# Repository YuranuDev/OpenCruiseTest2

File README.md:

# OpenCruise — Qt + aasdk 車載システム 簡易プロトタイプ

x86_64 PC 向けの車載システム試作。Qt Quick(QML) + C++ + CMake。Android Auto の接続・映像は同梱の `aasdk` を利用する。
**完成品ではなく、各機能を最低限つないだ動作確認用の仮システム**。

## 構成

```
OpenCruise/
├── CMakeLists.txt            トップ。aasdk をサブプロジェクトとして取り込み、app/ をビルド
├── aasdk/                    既存の aasdk（※ USB/USBWrapper.cpp のみ 1 か所修正。後述）
├── patches/                  aasdk に当てた修正の diff
├── scripts/                  開発用スクリプト(make_test_stream.sh=テスト映像(H.264)の生成 / bootsplash/=起動画面)
├── docs/                     設計メモ・調査データ・スクリーンショット
│   ├── *.md                  実装ガイド・Android Auto 接続フローの仕様
│   ├── reference/            aasdk_phone_data.csv など調査データ
│   └── screenshots/          画面の確認用スクリーンショット
└── app/
    ├── CMakeLists.txt        アプリ本体のビルド設定(ソース・QML・リソースの登録はここ)
    ├── src/                  C++(#include は src/ からの相対パス。例: "audio/AudioSettings.h")
    │   ├── main.cpp          起動・モデル生成・QML 公開・開発用オプション
    │   ├── core/             アプリ基盤: AppInfo / AppSettings / BootManager / Log / UiText
    │   ├── audio/            音: AudioSettings / SystemSound / AlsaAudio / AlsaSoundEffect
    │   ├── display/          画面: BrightnessController / DisplaySettings / DrmDisplay
    │   ├── ui/               UI 支援: ThemeSettings / WidgetStore / ClockModel / AlbumArtProvider
    │   ├── vehicle/          車両: VehicleDataManager / ReverseCamera
    │   ├── system/           SystemStats(CPU・メモリ・温度など)
    │   ├── notification/     NotificationManager / NotificationHistoryModel
    │   ├── androidauto/      Qt 側: AndroidAutoController / H264Decoder / VideoSurfaceItem / TestVideoFeeder / PhoneStatus
    │   └── aabackend/        Qt 非依存の aasdk 接続層（UI と分離。無効時はスタブ）
    │       ├── AasdkBackend.*    libusb・ioスレッド・USBHub、待機→接続→切断→待機のループ
    │       ├── AasdkSession.*    1接続ぶん。制御チャネル(バージョン/SSL/認証/サービス探索/Ping/切断)
    │       ├── AasdkVideoHandler.* 映像チャネル(Open/Setup/Start/データ受信/ACK/フォーカス)
    │       └── AasdkConfig.h     車載機として申告する値（解像度 dpi 等、暫定値を1か所に集約）
    ├── qml/                  QML(すべて 1 つのモジュール OpenCruise。他フォルダの型を使うファイルは `import OpenCruise` が必要)
    │   ├── Main.qml          ルート(ここだけ qml/ 直下)
    │   ├── theme/            Theme(シングルトン) / ThemeBackground
    │   ├── components/       共通部品: Panel / ActionButton / MaterialIcon / NumberText / StatCard / MarqueeText など
    │   ├── screens/          画面: HomeScreen / LauncherScreen / SettingsScreen / SplashScreen / ReverseCamera*
    │   ├── settings/         設定の部品(Settings* / WSStepper / WSTextField)
    │   │   └── pages/        設定の各ページ(SettingsPage*)
    │   ├── osd/              OSD(音量・明るさ)と通知(NotificationPopup / Bell / HistoryPanel)・AlarmClearButton
    │   ├── services/         画面を持たないシングルトン: VehicleHistory / WarningAlarm
    │   └── widgets/          ウィジェット(下の「ウィジェット」参照)
    └── resources/            実行ファイルに入れる/隣へコピーする素材
        ├── images/           ロゴなど(qrc に埋め込む)
        ├── fonts/            アイコンフォント(qrc に埋め込む)と日本語フォント(ビルド時に実行ファイルの隣の fonts/ へコピー)
        └── sounds/           効果音(ビルド時に実行ファイルの隣の sounds/ へコピー)
```

接続層 (`aabackend`) は Qt を一切含まず、UI は `AasdkBackend` の公開ヘッダだけを見る。
そのため aasdk が無い/接続できない環境でもアプリ全体が起動する（状態は「利用不可」「待機中」と表示）。

## ビルド

Ubuntu 24.04 で確認。必要パッケージ:

```bash
sudo apt install build-essential cmake ninja-build pkg-config \
  qt6-base-dev qt6-declarative-dev qml6-module-qtquick qml6-module-qtquick-controls \
  qml6-module-qtquick-layouts qml6-module-qtquick-window qml6-module-qtquick-templates \
  qml6-module-qtqml qml6-module-qtqml-workerscript \
  qt6-multimedia-dev qml6-module-qtmultimedia \
  libavcodec-dev libavutil-dev libswscale-dev \
  libboost-system-dev libboost-log-dev libprotobuf-dev protobuf-compiler libusb-1.0-0-dev libssl-dev \
  libasound2-dev
# 日本語表示用フォント（例）
sudo apt install fonts-noto-cjk

cmake -G Ninja -S . -B build -DCMAKE_BUILD_TYPE=Release
ninja -C build            # aasdk(約300ファイル)を含むため初回は数分〜十数分
./build/app/opencruise
```

- aasdk なしで UI だけビルド: `-DOPENCRUISE_ENABLE_AASDK=OFF`（Boost/libusb/protobuf 不要）
- aasdk は同梱のものを `SKIP_BUILD_PROTOBUF=ON` / `SKIP_BUILD_ABSL=ON`（システムの protobuf 3.21 を使用）でビルドする。
  Abseil が必要な新しい protobuf を使う場合はこの設定の見直しが必要。
- 実機接続には USB 権限が必要。aasdk の `DOCUMENTATION.md` にある udev ルール
  (`SUBSYSTEM=="usb", ATTR{idVendor}=="18d1", MODE="0666", GROUP="plugdev"`) を設定する。
  権限が無い場合、aasdk の `USBHub` は **エラーを出さず黙って無視する**ため、「待機中」のまま進まない。

### 開発用オプション

| オプション | 内容 |
|---|---|
| `--test-video <file>` | H.264 ファイルを映像として表示（スマホ無しでデコード/表示を確認）。`scripts/make_test_stream.sh` で生成 |
| `--screenshot <png> [--screenshot-delay <ms>]` | 画面を保存して終了 |
| `--open-settings` | 設定画面を開いた状態で起動 |
| `--fullscreen` | 全画面 |

ヘッドレス確認例: `QT_QPA_PLATFORM=offscreen QT_QUICK_BACKEND=software ./build/app/opencruise --screenshot out.png`

## 音量・明るさ

設定の「サウンド」「表示」から変更できるほか、キーボード(将来はステアリングスイッチ等)のショートカットで操作できる。

| ショートカット | 内容 |
|---|---|
| `Ctrl+Shift+V` / `Ctrl+Shift+B` | マスター音量を 5 % 下げる / 上げる(V = Volume。押しっぱなしで連続)。マスター音量と、マップ音声・音楽音声・システムの各音量バーをまとめて表示し、約 2.5 秒で自動で閉じる。表示中のバーはすべてタッチ/ドラッグで直接変更でき、押している間は閉じない |
| `Ctrl+Shift+K` / `Ctrl+Shift+L` | 画面の明るさを 10 % 下げる / 上げる(L = Light)。現在値のバーを表示し、約 2 秒で自動で閉じる |

すべて `Ctrl+Shift+文字` で統一している(将来の物理ボタンも、同じキーイベントを送れば同じ動作になる)。
音量・明るさは、隣り合う 2 つのキーで「左のキー = 下げる、右のキー = 上げる」にそろえている。
既存のキー(`Esc` / `F10` / `Menu` / `Meta`・`Super` / `Ctrl+Shift+D`)とは重ならない組み合わせにしてある。
メディアキーや `Ctrl+Alt+矢印` は、OS 側の音量・画面回転と二重に動くため使っていない。

- **マスター音量**(`audio/AudioSettings`): 3 つの音声系統すべてに掛かる共通の倍率(0〜100 %)。各系統の個別音量の設定値は変えずに保持する。
  再生器へ渡す値は `AudioSettings::gain(group)` の 1 か所で「個別 × マスター」に合成しており、`AudioPlayer` / `SystemSound` はこれだけを使う
  (マスターを別に掛けないこと。二重になる)。マイク(入力)は対象外。保存キーは `audio/masterVolume`。
- **画面の明るさ**(`display/BrightnessController`): 10〜100 %(0 にして画面が見えなくなるのを防ぐ)。保存キーは `display/brightness`。
  - Linux で `/sys/class/backlight/*/brightness` に書き込める場合は、バックライトを直接制御する。
  - 書き込めない場合(Windows、権限なし、外部ディスプレイなど)や書き込みに失敗した場合は、画面全体に黒い幕を重ねて暗くする方式に自動で切り替わる。
    どちらか一方だけを使うので、二重に暗くはならない。
  - バックライトを制御するには、そのファイルへ書き込める権限が必要(例: udev ルールでグループ書き込みを許可)。
  - バックライトは、保存された設定がある場合だけ起動時に値を反映する。終了時に元の値へは戻さない。

### 音の出し方(ALSA)

libasound(`libasound2-dev`)があるビルドでは、音を ALSA の機器へ直接出す・録る(PulseAudio / PipeWire を通さない。`audio/AlsaAudio`)。
設定の出力先・マイクの一覧は ALSA の機器(サウンドカードの PCM ごと。「システム既定」は ALSA の `default`)。
機器は音を出している間このアプリが使う(占有する。音が止まって 3 秒たつと手放す)が、アプリ内の音(マップ・音楽・システム・効果音)は
アプリの中で混ぜてから出すので、同じ機器を選んでも同時に鳴り、音量も別々。別々の機器にも分けられる。
効果音は `AlsaSoundEffect` で鳴らす(WAV は自前で読み、MP3 は QAudioDecoder で読む)。カードの抜き差しは `/proc/asound` を見て一覧を読み直す。
libasound が無いビルド(Windows など)は、これまでどおり Qt の音声入出力を使う。ログは `[AUDIO]`。
## テーマと背景

設定「表示 > テーマ」でアプリ全体の見た目を選べる(`ui/ThemeSettings`、QML では `themeSettings`。色と形は `qml/theme/Theme.qml`)。

| テーマ | 内容 |
|---|---|
| シンプル | これまでの見た目(平らな面・大きめの角丸・青のアクセント) |
| クラシック | 2000 年代ごろの車の内装に合う見た目。ガンメタ(夜)/シルバー(昼)の面に、ゆるいグラデーションと内側の細いハイライト、小さめの角丸。アクセント色(照明色)はアンバー・赤・青・緑・アイボリー・シアン |

背景(設定「表示 > 背景」): テーマに合わせる(シンプルは無地、クラシックはカーボン)/ 無地 / 模様(カーボン・ヘアライン・パンチング・ストライプ)/ 画像。
画像は `~/.local/share/OpenCruise/backgrounds` に PNG / JPEG を置くと選べる(並べる・画面を埋める・引き伸ばす)。濃さも変えられる。
面(カード・ボタン・ダイアログ)は `qml/components/Panel.qml` を使うと、テーマに合わせて描き分けられる。

### 飾りの画像(キャラなど)

初期画面のページごとに、好きな画像を好きな場所へ置ける(ウィジェットの後ろ・パネルの上・前、ステータスバーやナビバーの上も)。

1. `~/.local/share/OpenCruise/decorations` に画像(PNG / JPEG / WebP / GIF。キャラだけを置くなら透過 PNG)を入れる
2. 初期画面の「編集」→ 上のバーの「画像」→「画像を追加」で選ぶ(今のページの中央に置かれる)
3. ドラッグで移動(画面の中央・端に近づくと吸い付いて線が出る)。大きさは右下のつまみか、2 本指でつまむ(縦横比はそのまま)
4. 選ぶと下に操作パネルが出る: 濃さ・左右反転・重ね方・いちばん上へ・複製・削除(2 回押し)。上のバーの「元に戻す」で 1 つずつ戻せる

重ね方:

| 重ね方 | 出る場所 |
|---|---|
| 奥 | ウィジェット・バーの後ろ(ウィジェットの隙間から見える) |
| パネル | 各ウィジェットのパネル(カード)の上、メーターや文字の下。画面の同じ所にある画像が、パネルの形に切り抜かれて見える |
| 手前 | ウィジェットの前(タッチは下のウィジェットへ通す) |

「パネル」の角丸の切り抜きは、Qt 6.5 以降の MultiEffect、無ければ Qt5Compat の OpacityMask(`qml6-module-qt5compat-graphicaleffects`)を使う。
どちらも無いとき・ソフトウェア描画のときは四角く切り抜く(パネルの角の丸みの外へ少しはみ出る)。

置いた場所は `widgetStore.layoutJson` のページごとの `decor` に、画面に対する割合で保存する(画面の大きさが変わっても同じ所に出る)。
画像が見つからないものは、編集中だけ赤い枠で出る(消せる)。Android Auto 画面には出ない。
実装: `qml/widgets/DecorationStore.qml`(今のページの一覧・元に戻す)/ `DecorationLayer.qml`(奥・手前の表示)/
`DecorationPanelLayer.qml`(パネルの層。WidgetBase の中)/ `DecorationEditor.qml`・`DecorationPanel.qml`(置き直す操作)/
`DecorationPicker.qml`(追加パネル)。

## バックカメラ

バック信号が入ると、どの画面でもカメラの映像(全面)に切り替わり、切れると設定の秒数のあとで元の画面に戻る(`vehicle/ReverseCamera`、
QML では `reverseCamera`。画面は `qml/screens/ReverseCameraView.qml`、設定は「設定 > カメラ」)。

- バック信号: 今はダミーだけ。**Ctrl+Shift+R** か、設定の「ダミーのバック信号」で入/切する。
  将来の外部マイコン(バックランプの線を読む)からの入力は `ReverseCamera::setExternalReverse()` で受け、入力元を「外部」にする(通信は未実装)
- カメラ: Qt Multimedia の映像入力(Linux では V4L2)。UVC で認識されるキャプチャーボード・USB カメラを設定から選ぶ
  (機器の id で保存。「自動」は最初に見つかったもの。選んだ機器が抜けているときは、ほかのカメラに替えず「見つかりません」と出す)。
  形式は 1280x720 以下でいちばん大きく、フレームレートの高いものを選ぶ
- 映し方: 左右反転・ガイド線(距離の目安)・全体を表示 / 画面を埋める・すぐに映す(常にカメラを動かしておく)
- 映像の上には、左上にギアの表示(R・バック)、上の中央に警告マークつきの「周囲の安全を直接確認してください」を出す。
  バック中は閉じるボタンを出さない(信号が切れたら戻る)。設定の「映像を確認」で、バック信号なしで映像を確かめられる(右上の「確認を終わる」で戻る)
- 実行には `qml6-module-qtmultimedia` が要る。ログは `[CAMERA]`

## ウィジェット

初期画面の中央領域は、12 × 6 マスのウィジェット配置エリアになっている(時計・あいさつも、その中のウィジェット)。

| 操作 | 内容 |
|---|---|
| 長押し(約 0.3 秒)→ドラッグ | 持ち上げて移動。移動中だけ配置エリア(グリッド)と移動先の枠が滑らかに現れ、離すと最寄りの空きマスへスナップ。空きマスが無ければ元の位置へ戻る |
| ダブルタップ | 設定画面を持つウィジェットは設定ダイアログ(固有の設定 + サイズ + 削除)を開く |
| ナビバーの「編集」 | 編集モードに入る・出る(下記) |

編集モード(ナビバーの「編集」。Android Auto 画面ではメニューの「編集」):

| 操作 | 内容 |
|---|---|
| 上の編集バー | 「編集中」・ページの切り替え・選んだ数と操作(まとめて設定・削除・選択を解除)・このページを選択・全ページを選択・追加・完了。削除は 2 回押し |
| ページをまたいだ選択 | ページを移っても選択は残る(選んだ数は全ページの分。「2 個選択中(2 ページ)」)。「全ページを選択」→「まとめて設定」で、全ページのウィジェットの見た目をまとめて変えられる |
| ウィジェットをタップ | 選択 / 解除(グリッドが出て、各ウィジェットに名前と大きさ「3 x 2」が出る。中身は操作できない) |
| ウィジェットをドラッグ | すぐ移動(長押しは要らない)。選んだものの 1 つを動かすと、選択中のものが並びを保ってまとめて動く |
| 左上の丸いボタン(歯車) | そのウィジェットの設定 |
| 右上の丸いボタン(×) | 削除(1 回目で赤い「削除」に広がり、0.4〜3 秒の間にもう一度押すと消す) |
| まとめて設定 | 選んだウィジェットに同じ値を入れる。同じ種類だけならその種類の設定すべて、混ざっていれば共通の項目(枠・上部タイトル)だけ。範囲・単位・警告値・注意値・目盛り間隔・タイトル文字・サイズはそれぞれのまま |
| Android Auto の映像(Android Auto 画面) | ドラッグで置く角を、内側の角のつまみで大きさ(マス数)を変える。離したときに決まる |

追加パネル(編集バーの「追加」)は、ジャンル別タブ。「初期配置に戻す」も、ここ(2 回押しで実行)。

配置と設定は `QSettings`(`widgets/layout`、version つき JSON)へ保存する。

### ファイル構成(`app/qml/widgets/`)

| 場所 | 役割 | ファイル |
|---|---|---|
| `framework/` | 登録(新しいウィジェットを足すときに触る唯一の場所) | `WidgetRegistry.qml`(ジャンル・種類・既定サイズ/設定・初期配置) |
| `framework/` | 共通基盤 | `WidgetBase`(ウィジェットの土台) / `WidgetHost`(ドラッグ・スナップ・タップ振り分け・表示アニメーション) / `WidgetArea`(グリッド・衝突・保存) / `WidgetPages` / `PageBar` / `PageMenu` / `WidgetEditBar` |
| `framework/` | 設定・追加 UI | `WidgetSettingsBase` / `WidgetSettingsDialog` / `WidgetSettingsGroup` / `WidgetPicker`(入力部品の `WSStepper` / `WSTextField` は `settings/`) |
| `decoration/` | 装飾 | `Decoration*`(Store / Layer / Panel / PanelLayer / Editor / Picker / Effects) |
| `clock/` `greeting/` | 時計・あいさつ | `ClockWidget` / `GreetingWidget`(+ 各 `*Settings`) |
| `gauge/` `graph/` | 車載連携 | `GaugeWidget` / `GaugeSettings`(メーター共通。ターボ圧計・タコメーター・スピードメーター・水温計・燃料計。計測値の定義は `WidgetRegistry.gaugeSpecs`。アナログ+デジタル、単位切替、警告値・警告メッセージ。**モックデータ**) / `GraphWidget` / `GraphSettings` |
| `phonestatus/` | Android Auto 連携 | `PhoneStatusWidget`(スマホ状態。バッテリー残量は実データ、電波はモック) |
| `phonenotice/` `phonecall/` | 通知・通話連携 | `PhoneNoticeWidget`(スマホ通知。表示方法・カテゴリ別メッセージを設定可能。**モックの通知**) / `PhoneCallWidget` |
| `nowplaying/` `navigation/` | 再生中・ナビ | `NowPlayingWidget` / `NavigationWidget`(+ 各 `*Settings`) |

新しいウィジェットの追加手順: ① `widgets/<名前>/` フォルダを作り、`WidgetBase` を継承した qml を置く ② 設定が要るなら `WidgetSettingsBase` を継承した qml を作る
③ `WidgetRegistry.qml` に Component と `types` の 1 項目を足す ④ `app/CMakeLists.txt` の `QML_FILES` に足す(他フォルダの型を使うなら `import OpenCruise` を書く)。
設定が不要なウィジェットは `settings: null` にする(ダブルタップは何もしない)。独自のダブルタップ動作が欲しい場合は
`doubleTapAction: "custom"` にして `doubleTapped()` を受ける。

### Android Auto から取れる情報(`docs/reference/aasdk_phone_data.csv` の確認結果)

- 実データ: スマホのバッテリー(残量・残り時間・危険フラグ。`BatteryStatusNotification`。サービス宣言なしで届く)。`AasdkSession` →
  `AndroidAutoController` → `PhoneStatus::setBattery()`。バッテリー残量の単位(%)は実機での確認が必要。
- 未宣言のため届かない(現状モック): 電波強度(PhoneStatus サービス)、通知(GenericNotification サービス: id / text / icon のみ)、
  ナビ・再生中の曲。宣言を足したら `PhoneStatus::setSignal()` / `ingestNotice()` を呼ぶだけでウィジェットは実データに切り替わる。
- そもそも取れない: 通知の送信元アプリ名・本文、連絡先・通話履歴・メッセージ本文(プロトコルに無い)。通知のカテゴリは文面から推定する。

## 実装状況

### 実装済み

| 機能 | 状態 | 検証 |
|---|---|---|
| Qt Quick メイン画面（暗色、時計、接続状態、AA表示領域、CANパネル、設定ボタン） | 実装 | ビルド・起動・画面保存で確認 |
| 現在時刻表示 | 実装(時計ウィジェットへ移行) | 画面で確認(旧実装) |
| ウィジェットシステム(配置エリア・ドラッグ・スナップ・設定ダイアログ・追加パネル、時計/あいさつ/ターボ圧計/スマホ状態/スマホ通知) | コード実装 | **ビルド・実行とも未検証** |
| CAN 情報の仮表示（速度/回転数/水温/燃料、「ダミーデータ」と明示） | 実装 | 画面で確認 |
| 設定画面への遷移（StackView） | 実装 | 設定画面の描画を確認。ボタンのタップ操作は未確認 |
| 接続状態表示（利用不可/待機中/接続中/接続済み/映像受信中、切断理由の保持） | 実装 | 「利用不可」「待機中」「映像受信中(テスト)」を画面で確認 |
| 未接続・失敗時でもアプリ全体が起動 | 実装 | aasdk 無効/有効(USB機器なし)の両方で確認 |
| H.264 デコード → QImage → QML 表示 | 実装 | テスト映像(800x480)で表示を確認（aasdk 非経由） |
| aasdk 接続層（USBHub→AOAP→Messenger→制御/映像チャネル→切断→待機復帰） | **コード実装・ビルド成功** | **実機未検証** |
| 終了処理（スレッド停止・libusb 解放） | 実装 | 待機中の終了(約0.2秒)を確認。セッション中の終了は未検証 |
| マスター音量・音量ショートカット・音量表示 | コード実装 | **ビルド・実行とも未検証** |
| 画面の明るさ(設定・ショートカット・表示。バックライト/暗幕の自動切替) | コード実装 | **ビルド・実行とも未検証** |

### 検証できたこと / できていないこと

確認できた: aasdk を含むフルビルド成功(自作コードの警告 0)、起動と待機状態への遷移、10秒間の待機稼働、
サービス探索応答が protobuf として必須フィールドを満たすこと(`IsInitialized()`)、デコード/表示経路。

**未検証（実機が必要。「動作済み」とは扱わない）**: スマートフォンの検出、AOAP 切替、SSL ハンドシェイク、サービス探索の受理、
映像チャネルのセットアップ、実際の H.264 受信と表示、ACK の運用、切断時の復帰、再接続。

### aasdk が提供するもの / 追加実装したもの

| aasdk が提供 | 本プロジェクトで追加実装 |
|---|---|
| USB ホットプラグ検出・AOAP 切替 (`USBHub`) | libusb の初期化と **イベントループ専用スレッド**、io スレッド、待機⇄接続のループ |
| USB 転送・フレーム化・SSL 暗号化 (`USBTransport`/`Messenger`/`Cryptor`) | セッションの組み立てと終了処理 |
| チャネルの送受信と protobuf デコード（制御/映像） | **各メッセージへの応答ロジック**（ハンドシェイク手順、サービス探索応答の内容、Open/Setup/Start 応答、ACK、フォーカス応答、Ping） |
| 映像データの受信（H.264 の生バイト列まで） | **H.264 デコード**（FFmpeg）と画面表示 |

同梱の `aasdk/tools/simple` は AOAP ハンドシェイクのスタブで、Messenger/映像は含まない。完全なセッションの手順は
ヘッダ・実装・`.proto` から読み取った（根拠は各 `.cpp` 冒頭のコメントに記載）。

### 未実装

- 実 CAN 通信（ダミーのみ）
- タッチ入力・ステアリング操作の転送（InputSource）、センサー(走行状態等)、音声（再生/マイク）、Bluetooth、無線接続(Wi-Fi/TCP)
- 車載機側からの Ping 送信・タイムアウト検出
- 解像度/dpi の最適化（800x480・140dpi の暫定値。`AasdkConfig.h`）、GPU 描画（現状は `QQuickPaintedItem` のソフトウェア描画）
- 設定の保存、画面の多言語化（UI 文字列は日本語直書き）

## aasdk で見つけた問題と対処

1. **`USBWrapper::hotplugRegisterCallback` のダングリングポインタ（修正済み）**
   スタック上のハンドルのアドレスを `shared_ptr` に渡していたため、`USBHub::cancel()` でホットプラグコールバックが解除されず、
   破棄済みの `USBHub` に通知が飛ぶ恐れがあった。切断後に `USBHub` を作り直す設計に必須のため、ヒープ確保に修正
   （`patches/aasdk-usb-hotplug-handle.patch`。aasdk を更新する場合は再適用が必要）。
2. `Messenger::stop()` は受信キューを空にするだけで保留中の Promise を失敗させない → `transport->stop()` によるキャンセル経由で終了を伝播させている。
3. `Cryptor::deinit()` 後に `encrypt()` が呼ばれると `SSL*` が null でクラッシュし得る → 最後の参照者が消えた時に `deinit()` する（カスタムデリータ）。
4. バージョン応答の status は `uint16` を `MessageStatus` に単純キャストしており不一致値が `-1` にならない → 「`STATUS_SUCCESS` 以外は失敗」で判定。
5. `USBHub` は USB 機器の open 失敗を黙殺し、非 AOAP 機器の検出ごとに 1 秒 sleep する → io スレッドを 2 本にして影響を緩和。権限エラーは UI から判別できない。
6. `ControlServiceChannel::sendVoiceSessionFocusResponse` は実装が空（Promise が解決されない）→ 使っていない。

## 実機検証の際の見どころ（リスク）

- サービス探索で**映像サービスのみ**申告している。センサー/入力サービスが無いとスマートフォンが接続を維持しない可能性がある（未確認）。
  切断された場合は `AasdkVideoHandler::fillFeatures` と同様に `SensorSource`/`InputSource` の追加を検討する。
- `driver_position` は右ハンドル、音声フォーカス要求には「喪失」、ナビフォーカスには PROJECTED を返す暫定実装。
- ログは `[aa] [session] ...` `[aa] [video] ...` として標準エラーに出る。どこまで進んだかの切り分けに使える。
- `--test-video` で映像が出ても aasdk の受信が動いた証拠にはならない（状態表示に「aasdk 経由ではありません」と出る）。

## 使用素材・ライセンス

### 効果音: OtoLogic

アプリの効果音(`app/resources/sounds/`)には、[OtoLogic](https://otologic.jp) が配布している素材音源を使用しています。

- 素材: OtoLogic (https://otologic.jp)
- ライセンス: [CC BY 4.0](https://creativecommons.org/licenses/by/4.0/deed.ja)
- 利用規約: https://otologic.jp/free/license.html

素材を再配布するとき(このリポジトリを配布する場合も含む)は、このクレジット表記を引き継いでください。

### 音声: AivisSpeech

起動時のあいさつなどの音声(`app/resources/sounds/start/` の読み上げ音声)は、[AivisSpeech](https://aivis-project.com) で作成しました。

- AivisSpeech 本体: 生成した音声にクレジット表記の義務はありません(任意のクレジットとして記載しています)
- 音声合成モデル: 使ったモデルごとのライセンスに従います。AivisHub などで公開されている ACML / ACML-NC / CC0 のモデルは
  クレジット表記の義務がありません。ACML-NC のモデルは非商用に限られるため、商用で配布する場合はモデルのライセンスを確認してください
- 使用した音声合成モデル: (モデル名とライセンスを記入)

### クレジットの表示場所

アプリの画面内にも、同じクレジットを表示しています(設定 > 情報 > 使用素材・ライセンス)。

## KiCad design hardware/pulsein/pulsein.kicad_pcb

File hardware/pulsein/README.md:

# パルス入力アダプター PULSE-IN v1.0

関連：claude/power-board-design.md（v1.8）、claude/firmware-config-spec.md（v1.6）、claude/spice-verification.md（tb7）
KiCadデータ：OpenCruiseTest2/hardware/pulsein（生成スクリプト：gen/pulsein_sch.py、place_pulsein.py、route_pulsein.py、silk_pulsein.py、flow_pulsein.sh）

## 目的
車速パルス・タコ信号・外付けセンサーのパルスを、XIAO ESP32S3で読める3.3Vの信号に変換する。メイン基板は変更せず、J8／J9（JST-XH 4P）に小基板をつなぐ方式にした。

- 1枚で1チャンネル。J8につなげばD2、J9につなげばD3に入る（2チャンネルまで）
- 3チャンネル目以降は、J5（D6・D7・D10と5V・12V・GND）からケーブルで分岐すればつなげる。パルスの読み取りにアナログ入力は不要なので、D6・D7も使える

## 仕様
| 項目 | 値 |
|---|---|
| 入力 | 0〜16Vの方形波（プッシュプル）、またはオープンコレクタ（JP1でプルアップ） |
| しきい値 | 立ち上がり約1.8V／立ち下がり約1.0V（JP2を閉じると約5.8V／3.2V） |
| 周波数 | 〜約10kHz（入力のRCフィルタ τ=22µs） |
| 耐圧 | 22kの直列抵抗と4.7Vツェナーで保護。40Vのスパイクでも74LVC1G17の入力は4.7V前後（SPICE tb7） |
| 出力 | 3.3Vロジック（74LVC1G17のプッシュプル、100Ω直列） |
| 表示 | パルスに合わせてLEDが点滅する（配線確認用） |
| センサー用電源 | J2から5V（メインのF5 0.25A）と12V（VSW、メインのF4 1.1A）を出す |
| 外形 | 34×28mm、2層、M3穴1個 |

## 回路
- J2（入力、XH 4P）：1 SIG_IN／2 GND／3 +5V／4 +12V
- JP1（3端子ソルダージャンパー）：1-2で5Vプルアップ、2-3で12Vプルアップ（R1 4.7k）。初期は開放
- R2 22k → SIG_A。C1 1nF、DZ1 BZT52C4V7でGNDへ
- R3 10k＋JP2：閉じるとしきい値が上がる（ノイズの多い12V信号向け）。**5V／3.3Vの信号では閉じない**（入力が届かず、出力が出なくなる。SPICEで確認済み）
- U1 74LVC1G17（3.3V動作、シュミット）→ R4 100Ω → J1-4
- U2 XC6206P332（5V→3.3V）、C2・C3 1µF、C4 100nF
- R5 1k＋D1 LED：パルスの表示
- J1（メイン基板へ、XH 4P）：1 +12V（VSW_EXT）／2 +5V（5V_EXT）／3 GND／4 OUT。**メイン基板のJ8/J9と同じ並びなので、ストレートのXH 4Pケーブルでつなぐ**

## 信号ごとのジャンパー設定（目安）
| 信号 | JP1 | JP2 | 備考 |
|---|---|---|---|
| 車速パルス（12V方形波） | 開放 | 開放（ノイズが多ければ閉じる） | 実車で波形を確認する |
| 車速パルス（オープンコレクタ） | 1-2（5V）または2-3（12V） | 2-3のときだけ閉じてよい | テスターで、つないでいないときの電圧を見ると判別できる |
| タコ信号（12V方形波） | 開放 | 閉じる | |
| 外付けセンサー（5V／3.3V出力） | 開放 | 開放 | センサー電源はJ2の5Vから取れる |
| 外付けセンサー（オープンコレクタ） | 1-2（5V） | 開放 | |

## 製造（JLCPCB）
- jlc/pulsein_gerber_JLC.zip、jlc/pulsein_BOM_JLC.csv（12品目14点）、jlc/pulsein_CPL_JLC.csv
- J1・J2（JST XH B4B-XH-A）は、メイン基板と同じくAliExpressで買って手はんだする（BOMとCPLから除外）
- U1のLCSC番号はメイン基板のU5と同じ（C151394）。DZ1 BZT52C4V7（C173408）だけが拡張部品
- 検査：ERC 0件、DRC 違反0・未接続0、シルクとパッドの距離0.22mm以上（JLCの基準0.18mm以上）

## 実車での確認事項
- Keiの車速パルスとタコ信号の取り出し位置、波形（電圧・プッシュプルかオープンコレクタか）
- 車速パルスの1kmあたりのパルス数（日本車は2548パルス/kmが多い。GPSで合わせる）
- タコ信号の1回転あたりのパルス数（3気筒は1.5パルス/回転が多いが、車種で異なる）

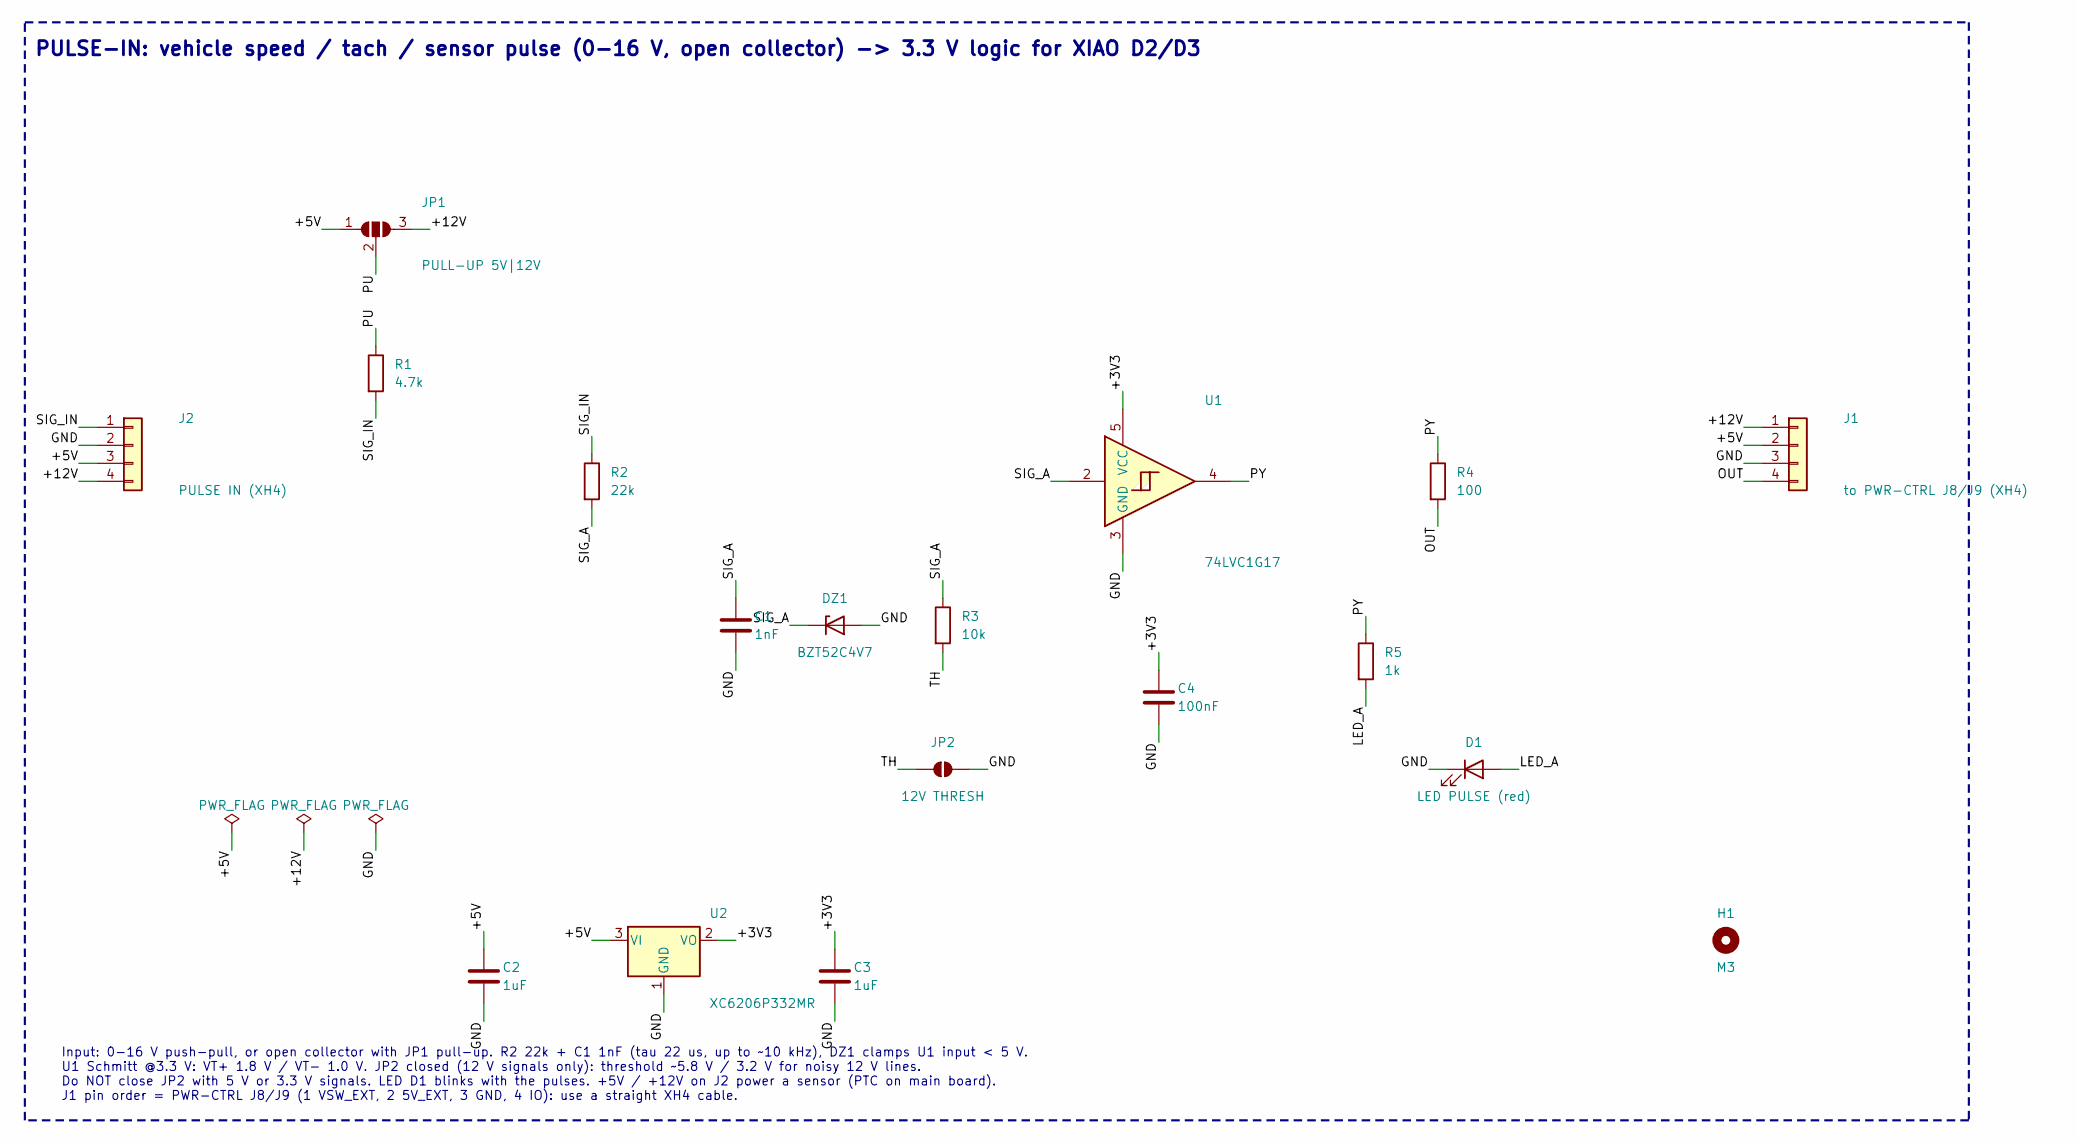
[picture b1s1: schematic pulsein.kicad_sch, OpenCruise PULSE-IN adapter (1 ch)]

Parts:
C1: 1nF; C_0603_1608Metric; LCSC C1588
C2, C3: 1uF; C_0603_1608Metric; LCSC C15849
C4: 100nF; C_0603_1608Metric; LCSC C14663
D1: LED PULSE (red); LED_0603_1608Metric; LCSC C2286
DZ1: BZT52C4V7; D_SOD-123; LCSC C173408
H1: M3; MountingHole_3.2mm_M3
J1: to PWR-CTRL J8/J9 (XH4); JST_XH_B4B-XH-A_1x04_P2.50mm_Vertical; LCSC C144395
J2: PULSE IN (XH4); JST_XH_B4B-XH-A_1x04_P2.50mm_Vertical; LCSC C144395
JP1: PULL-UP 5V|12V; SolderJumper-3_P1.3mm_Open_RoundedPad1.0x1.5mm
JP2: 12V THRESH; SolderJumper-2_P1.3mm_Open_RoundedPad1.0x1.5mm
R1: 4.7k; R_0603_1608Metric; LCSC C23162
R2: 22k; R_0603_1608Metric; LCSC C31850
R3: 10k; R_0603_1608Metric; LCSC C25804
R4: 100; R_0603_1608Metric; LCSC C22775
R5: 1k; R_0603_1608Metric; LCSC C21190
U1: 74LVC1G17; SOT-23-5; LCSC C151394
U2: XC6206P332MR; SOT-23; LCSC C5446

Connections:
+3V3: C3.1, C4.1, U1.5 (VCC), U2.2 (VO)
+5V: C2.1, J1.2, J2.3, JP1.1 (A), U2.3 (VI)
+12V: J1.1, J2.4, JP1.3 (B)
GND: C1.2, C2.2, C3.2, C4.2, D1.1 (K), DZ1.2 (A), J1.3, J2.2, JP2.2 (B), U1.3 (GND), U2.1 (GND)
LED_A: D1.2 (A), R5.2
OUT: J1.4, R4.2
PU: JP1.2 (C), R1.1
PY: R4.1, R5.1, U1.4
SIG_A: C1.1, DZ1.1 (K), R2.2, R3.1, U1.2
SIG_IN: J2.1, R1.2, R2.1
TH: JP2.1 (A), R3.2

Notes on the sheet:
PULSE-IN: vehicle speed / tach / sensor pulse (0-16 V, open collector) -> 3.3 V logic for XIAO D2/D3
Input: 0-16 V push-pull, or open collector with JP1 pull-up. R2 22k + C1 1nF (tau 22 us, up to ~10 kHz), DZ1 clamps U1 input < 5 V. U1 Schmitt @3.3 V: VT+ 1.8 V / VT- 1.0 V. JP2 closed (12 V signals only): threshold ~5.8 V / 3.2 V for noisy 12 V lines. Do NOT close JP2 with 5 V or 3.3 V signals. LE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

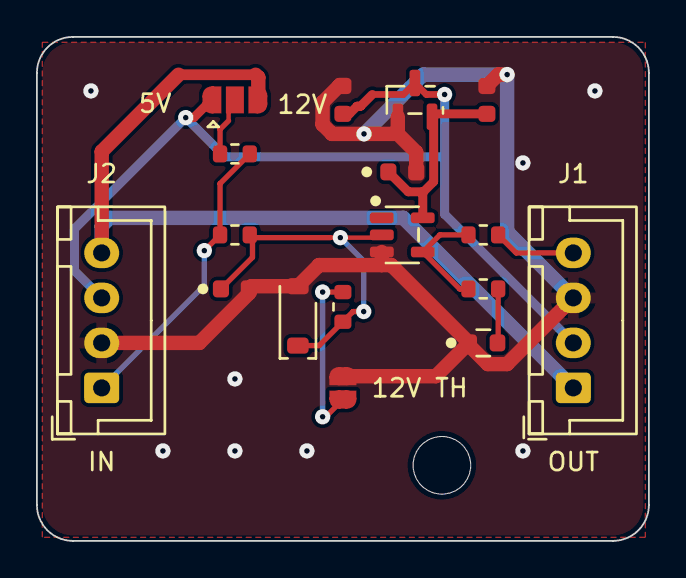
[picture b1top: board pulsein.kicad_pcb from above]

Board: 2 copper layers, 34.0 x 28.0 mm, 18 parts (0 on the bottom side), 11 nets.

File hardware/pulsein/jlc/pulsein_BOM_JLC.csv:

Comment,Designator,Footprint,LCSC Part #
1nF,"C1",C_0603_1608Metric,C1588
1uF,"C2,C3",C_0603_1608Metric,C15849
100nF,"C4",C_0603_1608Metric,C14663
LED PULSE (red),"D1",LED_0603_1608Metric,C2286
BZT52C4V7,"DZ1",D_SOD-123,C173408
4.7k,"R1",R_0603_1608Metric,C23162
22k,"R2",R_0603_1608Metric,C31850
10k,"R3",R_0603_1608Metric,C25804
100,"R4",R_0603_1608Metric,C22775
1k,"R5",R_0603_1608Metric,C21190
74LVC1G17,"U1",SOT-23-5,C151394
XC6206P332MR,"U2",SOT-23,C5446

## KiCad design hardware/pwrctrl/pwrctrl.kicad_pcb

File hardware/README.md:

# OpenCruise hardware (KiCad 9)

- pwrctrl/  : main power-control / vehicle-interface board (schematic + placement-proposal PCB, NOT routed yet)
- usbblock/ : USB-A inline VBUS back-feed blocker adapter (schematic)
- lib/      : project symbol/footprint library (OpenCruise) and 3D models
- gen/      : Python generators used to build the schematics/placement (kicad-cli + pcbnew 9.0)

Status v1.7 (2026-11-09): schematics complete, ERC 0 errors / 0 warnings. PCB layout pending review of placement_proposal.png.
Design notes: Claude project docs claude/power-board-design.md, firmware-config-spec.md, usb-adapter-design.md

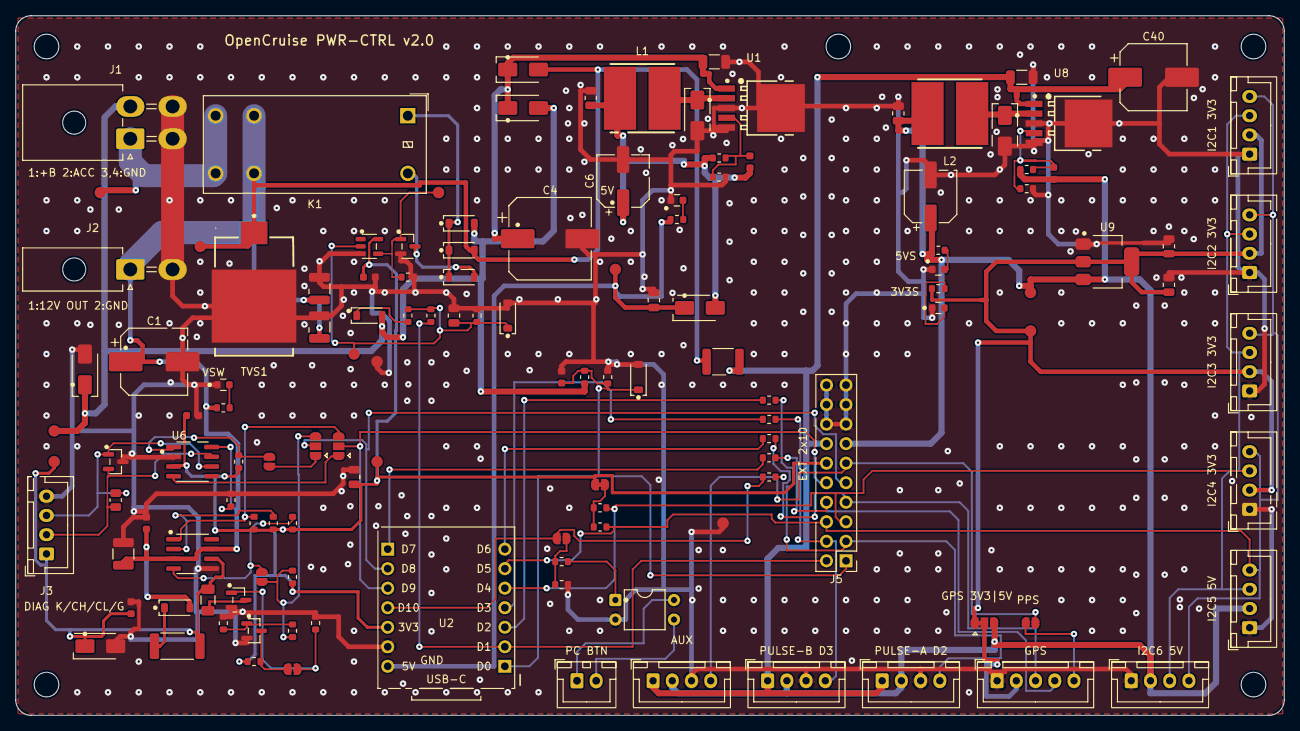
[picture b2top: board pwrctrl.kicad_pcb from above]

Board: 2 copper layers, 165.0 x 91.0 mm, 138 parts (0 on the bottom side), 63 nets.

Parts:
C1, C40: 100uF/50V; CP_Elec_8x10.5
C2, C3, C16: 10uF/50V; C_1210_3225Metric
C4: 470uF/50V; CP_Elec_10x12.5
C5, C41: 1uF/50V; C_1206_3216Metric
C6, C42: 100uF/16V; CP_Elec_6.3x5.4
C7, C9, C11, C13, C43, C45, C46: 10uF/25V; C_0805_2012Metric
C8, C44: 33nF; C_0603_1608Metric
C10, C12, C14, C15: 100nF; C_0603_1608Metric
C17: 220pF; C_0603_1608Metric
D1, D2, D3, D5, D10: 1N4148W; D_SOD-123
D7, D8, D9, D11, D12: SS34; D_SMA
F3: 0.1A PTC 60V; Fuse_1206_3216Metric
F4: 1.1A PTC 33V; Fuse_1812_4532Metric
H1, H2, H3, H4, H5: M3; MountingHole_3.2mm_M3
J1: Mini-Fit Jr 2x2 (+B/ACC/GND/GND); Molex_Mini-Fit_Jr_5569-04A2_2x02_P4.20mm_Horizontal
J2: Mini-Fit Jr 1x2 (VSW to DFR0946); Molex_Mini-Fit_Jr_5569-02A2_2x01_P4.20mm_Horizontal
J3: DIAG (K/CANH/CANL/GND); JST_XH_B4B-XH-A_1x04_P2.50mm_Vertical
J4: PC PWR SW; JST_XH_B2B-XH-A_1x02_P2.50mm_Vertical
J5: EXT 2x10 (debug / future); PinHeader_2x10_P2.54mm_Vertical
J6: I2C1 3V3 (XH4); JST_XH_B4B-XH-A_1x04_P2.50mm_Vertical
J7: I2C2 3V3 (XH4); JST_XH_B4B-XH-A_1x04_P2.50mm_Vertical
J8: PULSE-A D2 (XH4); JST_XH_B4B-XH-A_1x04_P2.50mm_Vertical
J9: PULSE-B D3 (XH4); JST_XH_B4B-XH-A_1x04_P2.50mm_Vertical
J10: XIAO socket D0-D6; PinSocket_1x07_P2.54mm_Vertical
J11: XIAO socket D7-5V; PinSocket_1x07_P2.54mm_Vertical
J12: I2C3 3V3 (XH4); JST_XH_B4B-XH-A_1x04_P2.50mm_Vertical
J13: I2C4 3V3 (XH4); JST_XH_B4B-XH-A_1x04_P2.50mm_Vertical
J14: I2C5 5V (XH4); JST_XH_B4B-XH-A_1x04_P2.50mm_Vertical
J15: I2C6 5V (XH4); JST_XH_B4B-XH-A_1x04_P2.50mm_Vertical
J16: GPS XH5 (3:RX of GPS<-D6, 4:TX of GPS->D7); JST_XH_B5B-XH-A_1x05_P2.50mm_Vertical
J17: AUX D10 (XH4); JST_XH_B4B-XH-A_1x04_P2.50mm_Vertical
JP1: CAN TX EN; SolderJumper-2_P1.3mm_Open_RoundedPad1.0x1.5mm
JP2: PC PWR BTN; SolderJumper-2_P1.3mm_Open_RoundedPad1.0x1.5mm
JP3: I2C PU (cut to remove); SolderJumper-2_P1.3mm_Bridged_RoundedPad1.0x1.5mm
JP4: TX: CAN|KL; SolderJumper-3_P1.3mm_Open_RoundedPad1.0x1.5mm
JP5: RX: CAN|KL; SolderJumper-3_P1.3mm_Open_RoundedPad1.0x1.5mm
JP6: KL TJA TX; SolderJumper-2_P1.3mm_Open_RoundedPad1.0x1.5mm
JP7: KL DIRECT; SolderJumper-2_P1.3mm_Open_RoundedPad1.0x1.5mm
JP8: GPS VCC 3V3|5V; SolderJumper-3_P1.3mm_Bridged12_RoundedPad1.0x1.5mm
JP9: PPS -> D10; SolderJumper-2_P1.3mm_Open_RoundedPad1.0x1.5mm
K1: G2RL-1A-E DC12; Relay_SPST_Omron_G2RL-1A-E
L1, L2: 100uH/1A; L_8040_SWPA8040
LED1: LED VSW (red); LED_0603_1608Metric
LED2: LED 5V (red); LED_0603_1608Metric
LED3: LED 5VS (red); LED_0603_1608Metric
LED4: LED 3V3S (red); LED_0603_1608Metric
Q1: BSS138; SOT-23
Q8: MMBT3904; SOT-23
Q9: 2N7002K; SOT-23
R1, R41, R42, R43: 1k; R_0603_1608Metric
R2: 1M; R_0603_1608Metric
R3: 470k; R_0603_1608Metric
R5: 47k; R_0603_1608Metric
R6: 6.8k; R_0603_1608Metric
R11, R13, R21, R23: 100k; R_0603_1608Metric
R12: 330; R_0603_1608Metric
R14: 510 1W; R_2512_6332Metric
R20, R22, R60, R61, R71, R72, R73: 10k; R_0603_1608Metric
R30, R31: 2.2k; R_0603_1608Metric
R40, R70: 4.7k; R_0603_1608Metric
R50, R52: 10.7k; R_0603_1608Metric
R51, R53: 3.3k; R_0603_1608Metric
R62: 120; R_0805_2012Metric
R80, R81, R82, R83, R84: 100; R_0603_1608Metric
TP1: VBAT_IN; TestPoint_Pad_D1.5mm
TP2: VSW; TestPoint_Pad_D1.5mm
TP3: ACC_IN; TestPoint_Pad_D1.5mm
TP4: +5V; TestPoint_Pad_D1.5mm
TP5: +3V3; TestPoint_Pad_D1.5mm
TP6: HOLD_N; TestPoint_Pad_D1.5mm
TP7: HOLD_G; TestPoint_Pad_D1.5mm
TP8: KLINE; TestPoint_Pad_D1.5mm
TP9, TP10: GND; TestPoint_Pad_D1.5mm
TP11: +5VS; TestPoint_Pad_D1.5mm
TP12: +3V3S; TestPoint_Pad_D1.5mm
TVS1: SM8S20A; DO-218AB
TVS2: SMAJ20A; D_SMA
TVS3: SMAJ24A; D_SMA
U1, U8: XL7015E1; TO-252-5_XL7015
U2: XIAO ESP32S3 (plug-in, buy separately); XIAO_Outline
U3: PC817 / AQY212; DIP-4_W7.62mm
U4: TJA1021T/20; SOIC-8_3.9x4.9mm_P1.27mm
U5: 74LVC1G17; SOT-23-5
U6: SN65HVD230; SOIC-8_3.9x4.9mm_P1.27mm
U7: PESD1CAN; SOT-23
U9: AMS1117-3.3; SOT-223-3_TabPin2
ZD1, ZD2: BZT52C3V6; D_SOD-123

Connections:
+3V3: C10.1, C13.1, C14.1, J5.12, J11.5, JP3.1, R22.1, R61.1, R70.1, R71.1, R72.1, R73.1, TP5.1, U5.5, U6.3
+3V3S: C45.1, C46.1, J6.2, J7.2, J12.2, J13.2, JP8.1, R43.1, TP12.1, U9.2
+5V: C9.1, D8.1, J11.7, R41.1, TP4.1
+5VS: C42.1, C43.1, C44.1, J5.13, J8.2, J9.2, J14.2, J15.2, J17.2, JP8.3, L2.2, R42.1, R52.1, TP11.1, U9.3
ACC_D: D3.1, R3.1
ACC_IN: D1.2, D3.2, D9.2, J1.2, R5.1, TP3.1, TVS2.1
ACC_SENSE: C12.1, J5.1, J10.1, R5.2, R6.1, ZD2.1
CANH: J3.2, R62.1, U6.7, U7.2
CANL: J3.3, R62.2, U6.6, U7.1
CAN_RS: R60.1, U6.8
CAN_RXD: JP5.1, U6.4
CAN_TXD: JP1.2, R61.2, U6.1
CAN_TXS: JP1.1, JP4.1
COIL_N: D5.2, K1.A2, Q1.3
COIL_P: D1.1, D2.1, D5.1, K1.A1
FB5: C8.2, R50.2, R51.1, U1.4
FB6: C44.2, R52.2, R53.1, U8.4
GND: C1.2, C2.2, C3.2, C4.2, C5.2, C6.2, C7.2, C9.2, C10.2, C11.2, C12.2, C13.2, C14.2, C15.2, C16.2, C17.2, C40.2, C41.2, C42.2, C43.2, C45.2, C46.2, D11.2, D12.2, J1.3, J1.4, J2.2, J3.4, J5.15, J5.16, J5.17, J5.18, J5.19, J5.20, J6.1, J7.1, J8.3, J9.3, J11.6, J12.1, J13.1, J14.1, J15.1, J16.1, J17.3, LED1.1, LED2.1, LED3.1, LED4.1, Q1.2, Q8.2, Q9.2, R2.2, R6.2, R11.2, R13.2, R21.2, R23.2, R51.2, R53.2, R60.2, TP9.1, TP10.1, TVS1.2, TVS2.2, TVS3.2, U1.3, U1.5, U1.6, U3.2, U4.5, U5.3, U6.2, U7.3, U8.3, U8.5, U8.6, U9.1, ZD1.2, ZD2.2
GPS_PPS: J16.5, JP9.1
GPS_VCC: J16.2, JP8.2
HOLD: J5.2, J10.2, R1.1
HOLD_G: Q1.1, R11.1, TP7.1, U5.4
HOLD_N: C11.1, R1.2, R2.1, R3.2, TP6.1, U5.2, ZD1.1
I2C_PU: JP3.2, R30.1, R31.1
IO_D2: J10.3, R80.1
IO_D3: J10.4, R81.1
IO_D6: J10.7, R82.1
IO_D7: J11.1, R83.1
IO_D10: J11.4, JP2.1, R84.1
KDRN: F3.1, Q9.3
KDRV: JP7.1, Q8.3, R22.2
KDRV_B: Q8.1, R20.2, R21.1
KGATE: JP7.2, Q9.1, R23.1
KLINE: C17.1, F3.2, J3.1, R14.2, TP8.1, TVS3.1, U4.6
KL_RXD: JP5.3, R70.2, U4.1
KL_SLP: R71.2, U4.2
KL_TXD: JP6.2, R72.2, U4.4
KL_TXS: JP4.3, JP6.1, R20.1, R73.2
KPU: D10.1, R14.1
LED1_A: LED1.2, R40.2
LED2_A: LED2.2, R41.2
LED3_A: LED3.2, R42.2
LED4_A: LED4.2, R43.2
OPTO_A: R12.2, U3.1
PWRB: JP2.2, R12.1, R13.1
PWR_SW+: J4.1, U3.4
PWR_SW-: J4.2, U3.3
P_D2: J5.3, J8.4, R80.2
P_D3: J5.4, J9.4, R81.2
P_D6: J5.7, J16.3, R82.2
P_D7: J5.8, J16.4, R83.2
P_D10: J5.11, J17.4, JP9.2, R84.2
SCL: J5.6, J6.4, J7.4, J10.6, J12.4, J13.4, J14.4, J15.4, R31.2
SDA: J5.5, J6.3, J7.3, J10.5, J12.3, J13.3, J14.3, J15.3, R30.2
SW5: D11.1, L1.1, U1.2
SW6: D12.1, L2.1, U8.2
V5REG: C6.1, C7.1, C8.1, D8.2, L1.2, R50.1
VBAT_IN: J1.1, K1.14, TP1.1
VEH_RX: J5.10, J11.3, JP5.2
VEH_TX: J5.9, J11.2, JP4.2
VIN5: C4.1, C5.1, D7.1, D9.1, U1.1
VSW: C1.1, C2.1, C3.1, C15.1, C16.1, D2.2, D7.2, D10.2, F4.1, J2.1, K1.13, R40.1, TP2.1, TVS1.1, U4.3, U4.7
VSW_EXT: C40.1, C41.1, F4.2, J5.14, J8.1, J9.1, J17.1, U8.1

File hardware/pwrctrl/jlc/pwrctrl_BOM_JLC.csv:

Comment,Designator,Footprint,LCSC Part #
100uF/50V,"C1,C40",CP_Elec_8x10.5,C48935390
10uF/50V,"C2,C3,C16",C_1210_3225Metric,C138687
470uF/50V,C4,CP_Elec_10x12.5,C22469994
1uF/50V,"C5,C41",C_1206_3216Metric,C1848
100uF/16V,"C6,C42",CP_Elec_6.3x5.4,C2887276
10uF/25V,"C7,C9,C11,C13,C43,C45,C46",C_0805_2012Metric,C15850
33nF,"C8,C44",C_0603_1608Metric,C106856
100nF,"C10,C12,C14,C15",C_0603_1608Metric,C14663
220pF,C17,C_0603_1608Metric,C1603
1N4148W,"D1,D2,D3,D5,D10",D_SOD-123,C81598
SS34,"D7,D8,D9,D11,D12",D_SMA,C8678
0.1A PTC 60V,F3,Fuse_1206_3216Metric,C70065
1.1A PTC 33V,F4,Fuse_1812_4532Metric,C269134
G2RL-1A-E DC12,K1,Relay_SPST_Omron_G2RL-1A-E,C1564126
100uH/1A,"L1,L2",L_8040_SWPA8040,C83468
LED VSW (red),LED1,LED_0603_1608Metric,C2286
LED 5V (red),LED2,LED_0603_1608Metric,C2286
LED 5VS (red),LED3,LED_0603_1608Metric,C2286
LED 3V3S (red),LED4,LED_0603_1608Metric,C2286
BSS138,Q1,SOT-23,C82045
MMBT3904,Q8,SOT-23,C20526
2N7002K,Q9,SOT-23,C85047
1k,"R1,R41,R42,R43",R_0603_1608Metric,C21190
1M,R2,R_0603_1608Metric,C22935
470k,R3,R_0603_1608Metric,C23178
47k,R5,R_0603_1608Metric,C25819
6.8k,R6,R_0603_1608Metric,C23212
100k,"R11,R13,R21,R23",R_0603_1608Metric,C25803
330,R12,R_0603_1608Metric,C23138
510 1W,R14,R_2512_6332Metric,C2934121
10k,"R20,R22,R60,R61,R71,R72,R73",R_0603_1608Metric,C25804
2.2k,"R30,R31",R_0603_1608Metric,C4190
4.7k,"R40,R70",R_0603_1608Metric,C23162
10.7k,"R50,R52",R_0603_1608Metric,C5153968
3.3k,"R51,R53",R_0603_1608Metric,C22978
100,"R80,R81,R82,R83,R84",R_0603_1608Metric,C22775
SM8S20A,TVS1,DO-218AB,C371081
SMAJ20A,TVS2,D_SMA,C908772
SMAJ24A,TVS3,D_SMA,C908774
XL7015E1,"U1,U8",TO-252-5_XL7015,C73013
PC817 / AQY212,U3,DIP-4_W7.62mm,C5350
TJA1021T/20,U4,SOIC-8_3.9x4.9mm_P1.27mm,C128810
74LVC1G17,U5,SOT-23-5,C151394
SN65HVD230,U6,SOIC-8_3.9x4.9mm_P1.27mm,C12084
PESD1CAN,U7,SOT-23,C15771
AMS1117-3.3,U9,SOT-223-3_TabPin2,C6186
BZT52C3V6,"ZD1,ZD2",D_SOD-123,C173412

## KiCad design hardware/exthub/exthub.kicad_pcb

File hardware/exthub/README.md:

# 拡張ハブ EXT-HUB v1.0 ＋ 拡張の割り当て表

> **v2.0でメイン基板に統合済み。この基板は製造しない。** ピンの割り当て・I2Cアドレス予約表（5章）は引き続き有効。ポートの配置はメイン基板（power-board-design.md 8章、pwrctrl/LAYOUT.md）を参照。メイン基板ではQwiicを廃止し、I2C1〜4もJST XHになった。プルアップはメイン基板の2.2k（1組）だけ

関連：claude/power-board-design.md（v1.8）、claude/firmware-config-spec.md（v1.7）、claude/pulse-input-adapter.md
KiCadデータ：OpenCruiseTest2/hardware/exthub（生成スクリプト：gen/exthub_sch.py、place_exthub.py、route_exthub.py、silk_exthub.py、flow_exthub.sh）

## 1. 考え方
- XIAOの空きピンは少ないので、**「どのピンを何に使うか」を先に決め、用途ごとに専用のコネクタを常設する**
- センサー類は基本的に**I2C**でつなぐ（2本の線に何台でもつなげる）。I2Cのコネクタを6個用意し、どこに挿しても同じバスにつながる
- メイン基板は変更しない。メイン基板のJ5（2×10）からフラットケーブルで拡張ハブにつなぐ
- 拡張ハブは**自前の5V・3.3V電源**を持つ（メイン基板のVSW＝12Vから作る）。センサーを増やしても、マイコンの電源に負担をかけない

## 2. XIAOのピン割り当て（確定）
| ピン | 用途 | つなぐ場所 | 変更 |
|---|---|---|---|
| D0 | ACC検知・電圧計 | メイン基板内 | 不可 |
| D1 | HOLD（リレー保持） | メイン基板内 | 不可（拡張ハブには出さない） |
| D2 | パルス入力A（車速） | ハブ PULSE-A／メイン J8 | 他の用途も可 |
| D3 | パルス入力B（回転数） | ハブ PULSE-B／メイン J9 | 他の用途も可 |
| D4／D5 | I2C（SDA／SCL） | ハブ I2C1〜6／メイン J6・J7 | 不可（センサー用のバス） |
| D6／D7 | UART（GPS） | ハブ GPS | GPSを使わなければ2本目のI2Cなどに使える |
| D8／D9 | 車両通信（CAN／K-Line） | メイン基板内 | 不可 |
| D10 | 予備（PPS・1-Wire・割り込み） | ハブ AUX（またはGPSのPPS、JP3） | 用途を1つ選ぶ |

## 3. 拡張ハブのコネクタ
| 名前 | 記号 | コネクタ | ピン（1→） | 用途 |
|---|---|---|---|---|
| メイン基板から | J1 | 2×10 ボックスヘッダー | メインJ5と同じ番号 | フラットケーブル（赤い線が1番） |
| I2C1〜I2C4 | J2〜J5 | Qwiic（JST SH 4P） | GND／3V3／SDA／SCL | 3.3Vのセンサー基板（Qwiic・STEMMA QT）をケーブル1本で |
| I2C5・I2C6 | J6・J7 | JST XH 4P | GND／5V／SDA／SCL | 5V電源が必要なモジュール、少し長い配線。信号は3.3V |
| GPS | J8 | JST XH 5P | GND／VCC／RX(D6)／TX(D7)／PPS | GPSモジュール。VCCはJP2で3.3V（初期）か5V |
| PULSE-A | J9 | JST XH 4P | 12V／5V／GND／D2 | PULSE-INアダプター（車速） |
| PULSE-B | J10 | JST XH 4P | 12V／5V／GND／D3 | PULSE-INアダプター（回転数） |
| AUX | J11 | JST XH 4P | 12V／5V／GND／D10 | 1-Wire温度センサー、割り込み入力、スイッチなど |

- PULSE-A／B・AUXはメイン基板のJ8/J9と同じピン順。PULSE-INアダプターはどちらにもストレートのケーブルでつなげる（ただし同じピンを2か所で使わない）
- GPIO（D2・D3・D6・D7・D10）には100Ωの直列抵抗を入れ、配線ミスからXIAOのピンを守る
- ジャンパー：JP1（I2Cプルアップ2.7k、初期は接続。切ると外れる）、JP2（GPS電源 1-2:3.3V／2-3:5V、初期は3.3V）、JP3（GPSのPPSをD10へ。初期は開放）

## 4. 電源
| 電源 | 作り方 | 容量（合計） | 使う場所 |
|---|---|---|---|
| 12V | メイン基板のVSW_EXT（F4 1.1A） | 拡張ハブの5V電源分を引いて約0.7A | PULSE／AUXの1番ピン（12Vセンサー用） |
| 5V | XL7015（メイン基板と同じ回路、5.3V） | 約0.7A | I2C5・6、PULSE／AUXの2番、GPS（JP2） |
| 3.3V | AMS1117-3.3（5Vから） | 約0.4A（発熱の上限） | I2C1〜4、GPS（初期）、I2Cプルアップ |

- 拡張ハブはACC ON（リレーON）の間だけ動く。エンジンを切れば電源は切れる（暗電流ゼロのまま）
- メイン基板のJ5の3V3（12番）と5V_EXT（13番）は使わない（電源をぶつけないため）

## 5. I2Cアドレスの割り当て（ぶつからないように予約）
| アドレス | 用途（予定） | 部品の例 |
|---|---|---|
| 0x20〜0x27 | I/Oエキスパンダー（スイッチ・LED・リレー） | PCA9555／MCP23017 |
| 0x3C | 小型表示器 | SSD1306 |
| 0x40〜0x45 | 電流・電力 | INA226／INA219 |
| 0x48〜0x4B | アナログ入力（油温・油圧・ブースト・燃料など） | ADS1115（4台で16ch） |
| 0x68／0x69 | 加速度・ジャイロ | ICM-42688／MPU-6050 |
| 0x70 | I2C切り替え（同じアドレスの機器が必要になったとき） | TCA9548A |
| 0x76／0x77 | 温度・湿度・気圧 | BME280 |
| 0x42 | GPSのI2C（使わない。GPSはUARTでつなぐ） | u-blox |

- 新しい機器を足すときはこの表に追記してから買う
- I2Cは400kHzで使う。プルアップは、ハブの2.7kとメイン基板の4.7k（JP3）が並列になり約1.7k（400kHzに適した値）
- 配線はハブから各センサーまで1m以内を目安にする。エンジンルームなど遠い場所は、PCA9615（差動I2C）や別のマイコン＋CANを検討する

## 6. 製造（JLCPCB）
- jlc/exthub_gerber_JLC.zip、jlc/exthub_BOM_JLC.csv（16行・24点）、jlc/exthub_CPL_JLC.csv
- コネクタ（J1〜J11）はAliExpressで買って手はんだする（BOM/CPLから除外）
- 外形92×58mm、2層、M3穴4個
- 検査：ERC 0件、DRC 違反0・未接続0、シルクとパッドの距離0.22mm以上

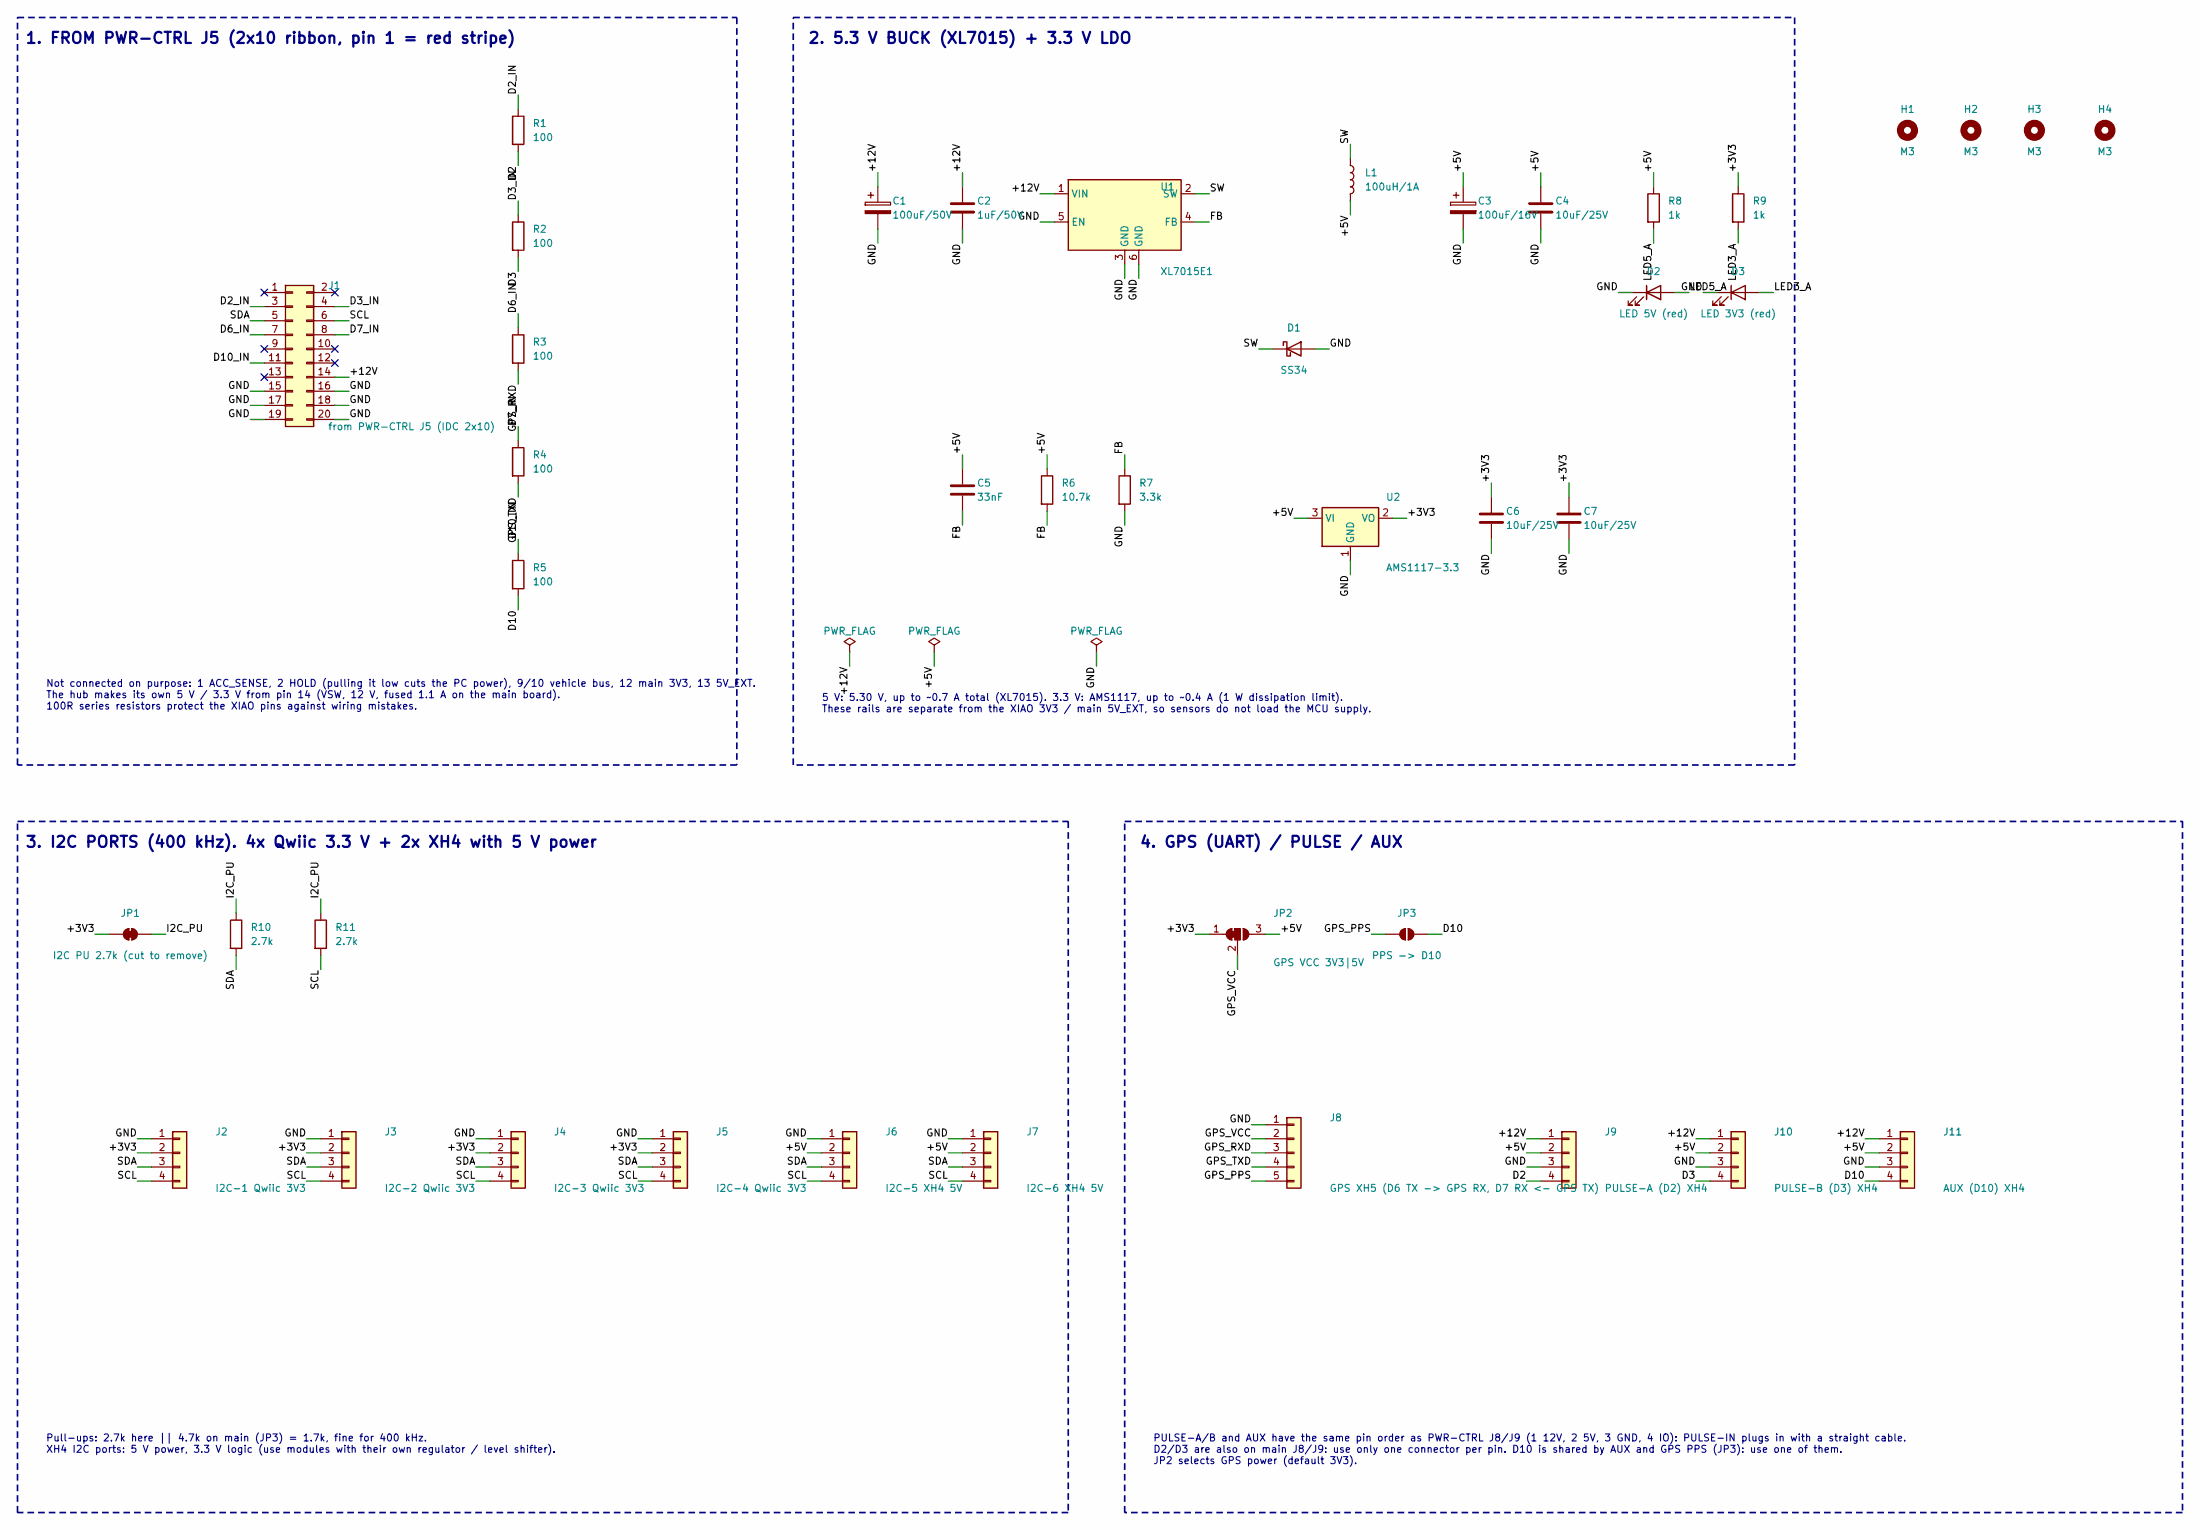
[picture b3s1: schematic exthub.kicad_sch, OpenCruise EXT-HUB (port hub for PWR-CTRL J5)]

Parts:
C1: 100uF/50V; CP_Elec_8x10.5; LCSC C48935390
C2: 1uF/50V; C_1206_3216Metric; LCSC C1848
C3: 100uF/16V; CP_Elec_6.3x5.4; LCSC C2887276
C4, C6, C7: 10uF/25V; C_0805_2012Metric; LCSC C15850
C5: 33nF; C_0603_1608Metric; LCSC C106856
D1: SS34; D_SMA; LCSC C8678
D2: LED 5V (red); LED_0603_1608Metric; LCSC C2286
D3: LED 3V3 (red); LED_0603_1608Metric; LCSC C2286
H1, H2, H3, H4: M3; MountingHole_3.2mm_M3
J1: from PWR-CTRL J5 (IDC 2x10); IDC-Header_2x10_P2.54mm_Vertical
J2: I2C-1 Qwiic 3V3; JST_SH_SM04B-SRSS-TB_1x04-1MP_P1.00mm_Horizontal; LCSC C160404
J3: I2C-2 Qwiic 3V3; JST_SH_SM04B-SRSS-TB_1x04-1MP_P1.00mm_Horizontal; LCSC C160404
J4: I2C-3 Qwiic 3V3; JST_SH_SM04B-SRSS-TB_1x04-1MP_P1.00mm_Horizontal; LCSC C160404
J5: I2C-4 Qwiic 3V3; JST_SH_SM04B-SRSS-TB_1x04-1MP_P1.00mm_Horizontal; LCSC C160404
J6: I2C-5 XH4 5V; JST_XH_B4B-XH-A_1x04_P2.50mm_Vertical; LCSC C144395
J7: I2C-6 XH4 5V; JST_XH_B4B-XH-A_1x04_P2.50mm_Vertical; LCSC C144395
J8: GPS XH5 (D6 TX -> GPS RX, D7 RX <- GPS TX); JST_XH_B5B-XH-A_1x05_P2.50mm_Vertical; LCSC C157991
J9: PULSE-A (D2) XH4; JST_XH_B4B-XH-A_1x04_P2.50mm_Vertical; LCSC C144395
J10: PULSE-B (D3) XH4; JST_XH_B4B-XH-A_1x04_P2.50mm_Vertical; LCSC C144395
J11: AUX (D10) XH4; JST_XH_B4B-XH-A_1x04_P2.50mm_Vertical; LCSC C144395
JP1: I2C PU 2.7k (cut to remove); SolderJumper-2_P1.3mm_Bridged_RoundedPad1.0x1.5mm
JP2: GPS VCC 3V3|5V; SolderJumper-3_P1.3mm_Bridged12_RoundedPad1.0x1.5mm
JP3: PPS -> D10; SolderJumper-2_P1.3mm_Open_RoundedPad1.0x1.5mm
L1: 100uH/1A; L_8040_SWPA8040; MPN SWPA8040S101MT; LCSC C83468
R1, R2, R3, R4, R5: 100; R_0603_1608Metric; LCSC C22775
R6: 10.7k; R_0603_1608Metric; LCSC C5153968
R7: 3.3k; R_0603_1608Metric; LCSC C22978
R8, R9: 1k; R_0603_1608Metric; LCSC C21190
R10, R11: 2.7k; R_0603_1608Metric; LCSC C13167
U1: XL7015E1; TO-252-5_XL7015; LCSC C73013
U2: AMS1117-3.3; SOT-223-3_TabPin2; LCSC C6186

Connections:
+3V3: C6.1, C7.1, J2.2, J3.2, J4.2, J5.2, JP1.1 (A), JP2.1 (A), R9.1, U2.2 (VO)
+5V: C3.1, C4.1, C5.1, J6.2, J7.2, J9.2, J10.2, J11.2, JP2.3 (B), L1.2, R6.1, R8.1, U2.3 (VI)
+12V: C1.1, C2.1, J1.14, J9.1, J10.1, J11.1, U1.1 (VIN)
D2: J9.4, R1.2
D2_IN: J1.3, R1.1
D3: J10.4, R2.2
D3_IN: J1.4, R2.1
D6_IN: J1.7, R3.1
D7_IN: J1.8, R4.1
D10: J11.4, JP3.2 (B), R5.2
D10_IN: J1.11, R5.1
FB: C5.2, R6.2, R7.1, U1.4 (FB)
GND: C1.2, C2.2, C3.2, C4.2, C6.2, C7.2, D1.2 (A), D2.1 (K), D3.1 (K), J1.15, J1.16, J1.17, J1.18, J1.19, J1.20, J2.1, J3.1, J4.1, J5.1, J6.1, J7.1, J8.1, J9.3, J10.3, J11.3, R7.2, U1.3 (GND), U1.5 (EN), U1.6 (GND), U2.1 (GND)
GPS_PPS: J8.5, JP3.1 (A)
GPS_RXD: J8.3, R3.2
GPS_TXD: J8.4, R4.2
GPS_VCC: J8.2, JP2.2 (C)
I2C_PU: JP1.2 (B), R10.1, R11.1
LED3_A: D3.2 (A), R9.2
LED5_A: D2.2 (A), R8.2
SCL: J1.6, J2.4, J3.4, J4.4, J5.4, J6.4, J7.4, R11.2
SDA: J1.5, J2.3, J3.3, J4.3, J5.3, J6.3, J7.3, R10.2
SW: D1.1 (K), L1.1, U1.2 (SW)

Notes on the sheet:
1. FROM PWR-CTRL J5 (2x10 ribbon, pin 1 = red stripe)
Not connected on purpose: 1 ACC_SENSE, 2 HOLD (pulling it low cuts the PC power), 9/10 vehicle bus, 12 main 3V3, 13 5V_EXT. The hub makes its own 5 V / 3.3 V from pin 14 (VSW, 12 V, fused 1.1 A on the main board). 100R series resistors protect the XIAO pins against wiring mistakes.
2. 5.3 V BUCK (XL7015) + 3.3 V LDO
5 V: 5.30 V, up to ~0.7 A total (XL7015). 3.3 V: AMS1117, up to ~0.4 A (1 W dissipation limit). These rails are separate from the XIAO 3V3 / main 5V_EXT, so sensors do not load the MCU supply.
3. I2C PORTS (400 kHz). 4x Qwiic 3.3 V + 2x XH4 with 5 V power
Pull-ups: 2.7k here || 4.7k on main (JP3) = 1.7k, fine for 400 kHz. XH4 I2C ports: 5 V power, 3.3 V logic (use modules with their own regulator / level shifter).
4. GPS (UART) / PULSE / AUX
PULSE-A/B and AUX have the same pin order as PWR-CTRL J8/J9 (1 12V, 2 5V, 3 GND, 4 IO): PULSE-IN plugs in with a straight cable. D2/D3 are also on main J8/J9: use only one connector per pin. D10 is shared by AUX and GPS PPS (JP3): use one of them. JP2 selects GPS power (default 3V3).
